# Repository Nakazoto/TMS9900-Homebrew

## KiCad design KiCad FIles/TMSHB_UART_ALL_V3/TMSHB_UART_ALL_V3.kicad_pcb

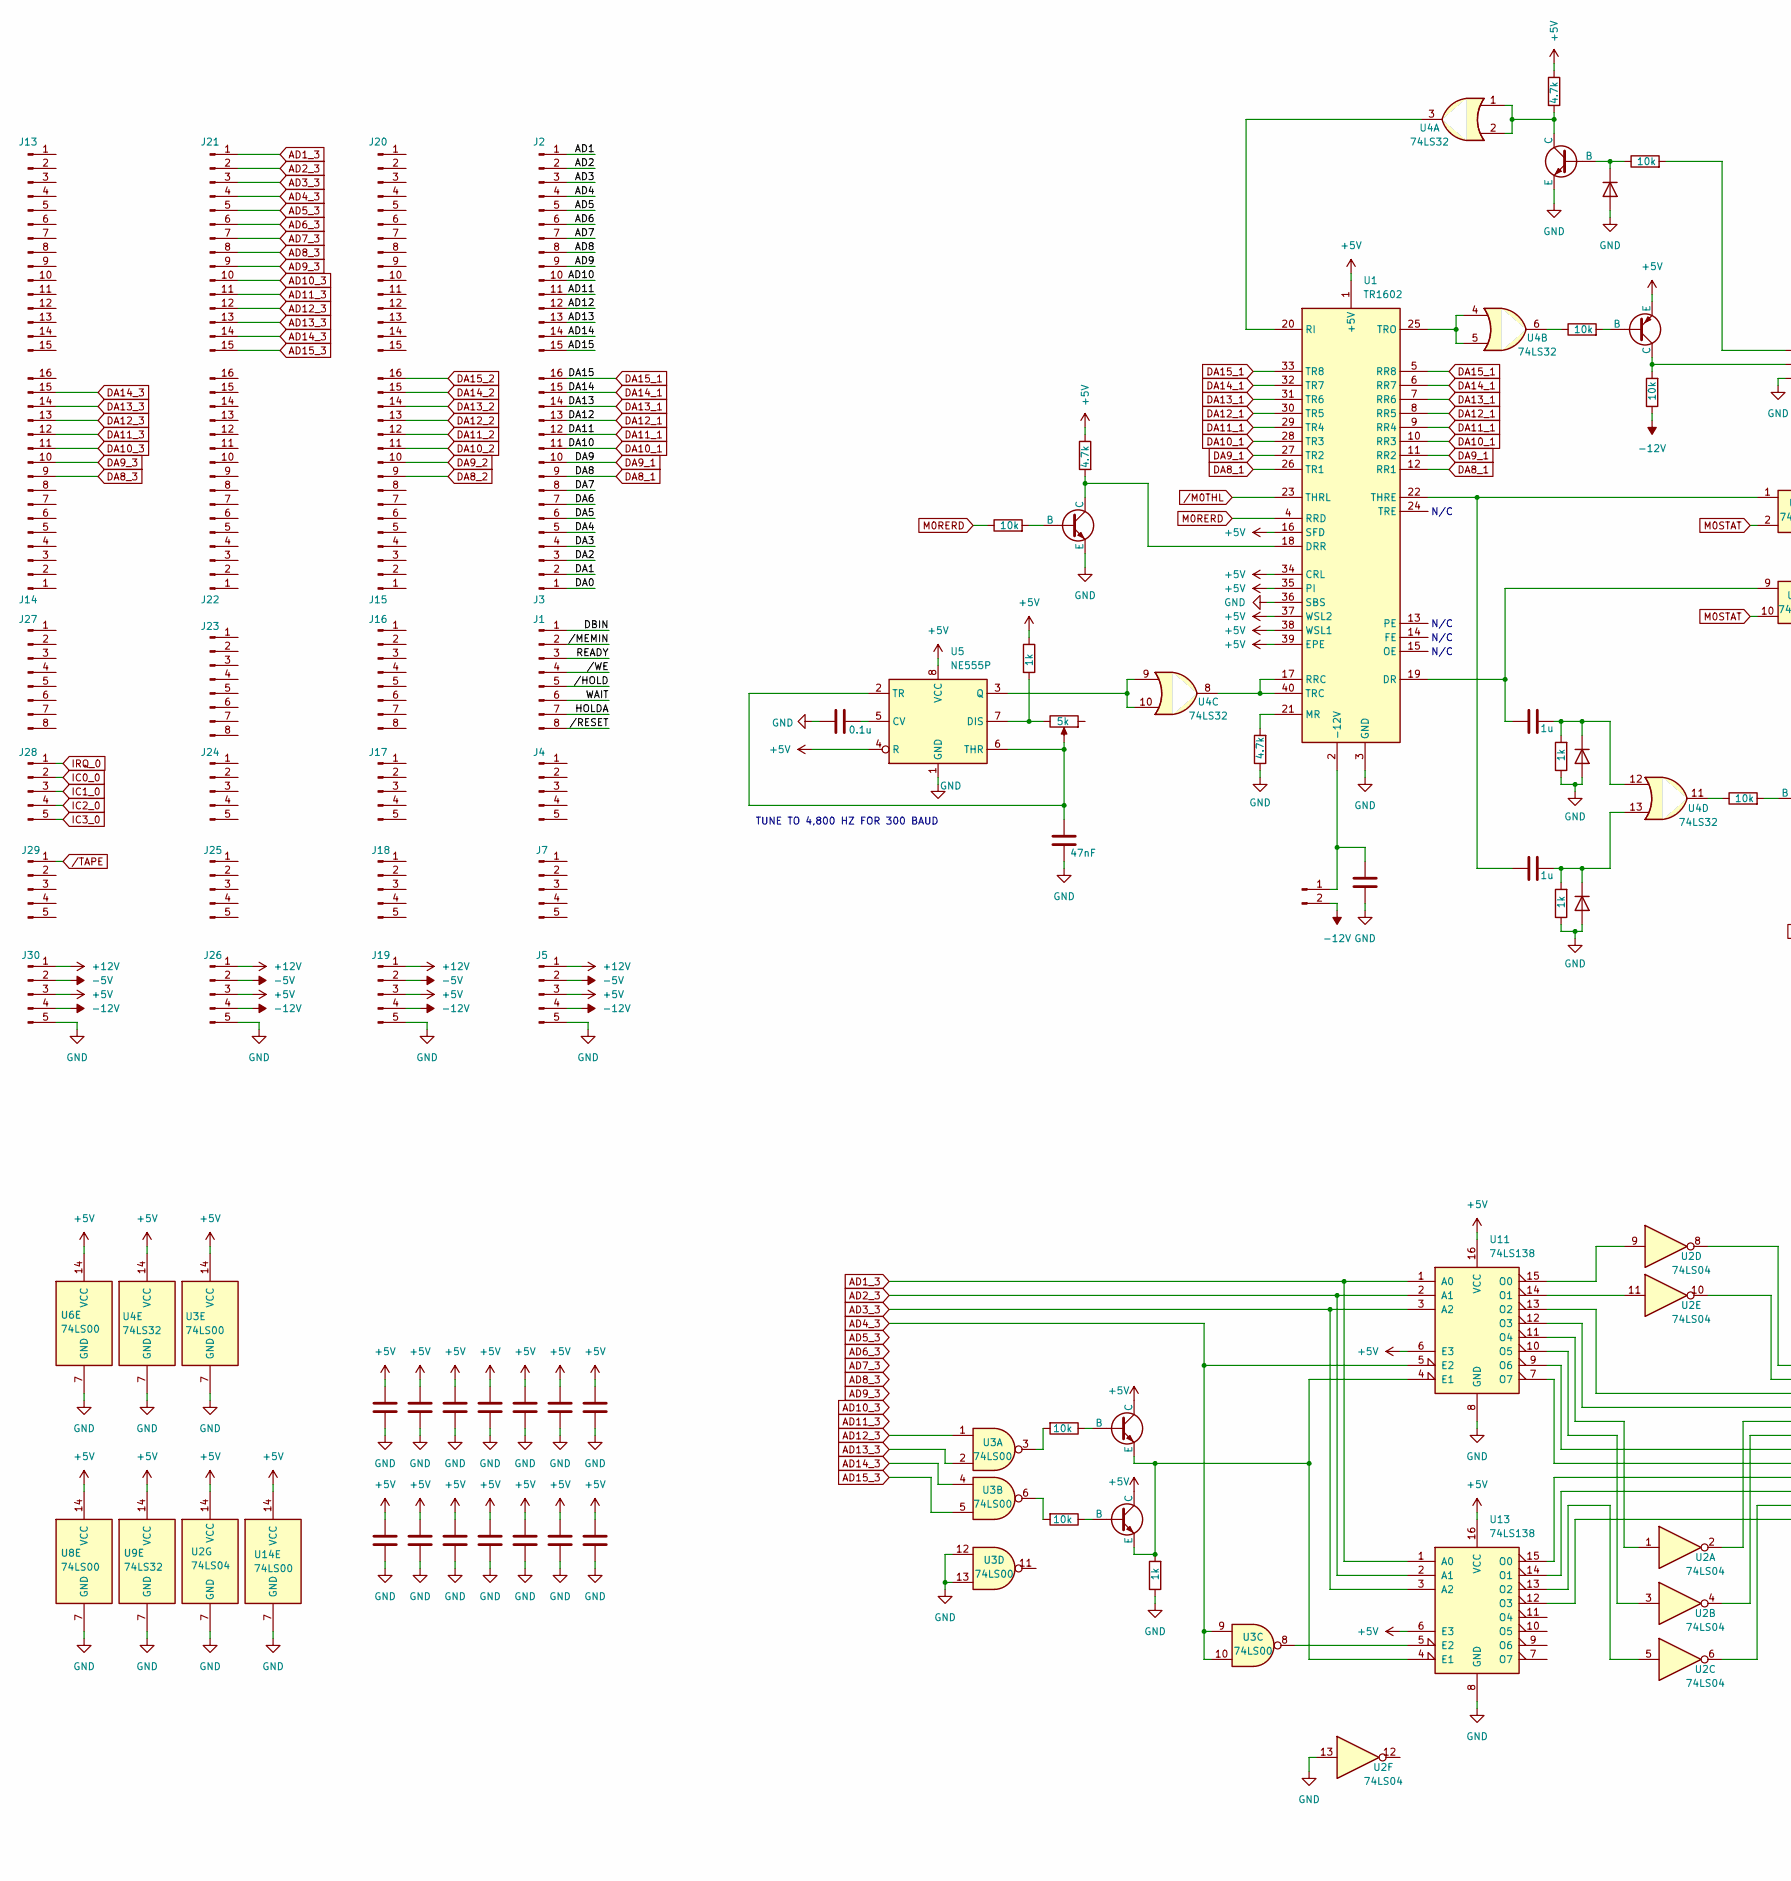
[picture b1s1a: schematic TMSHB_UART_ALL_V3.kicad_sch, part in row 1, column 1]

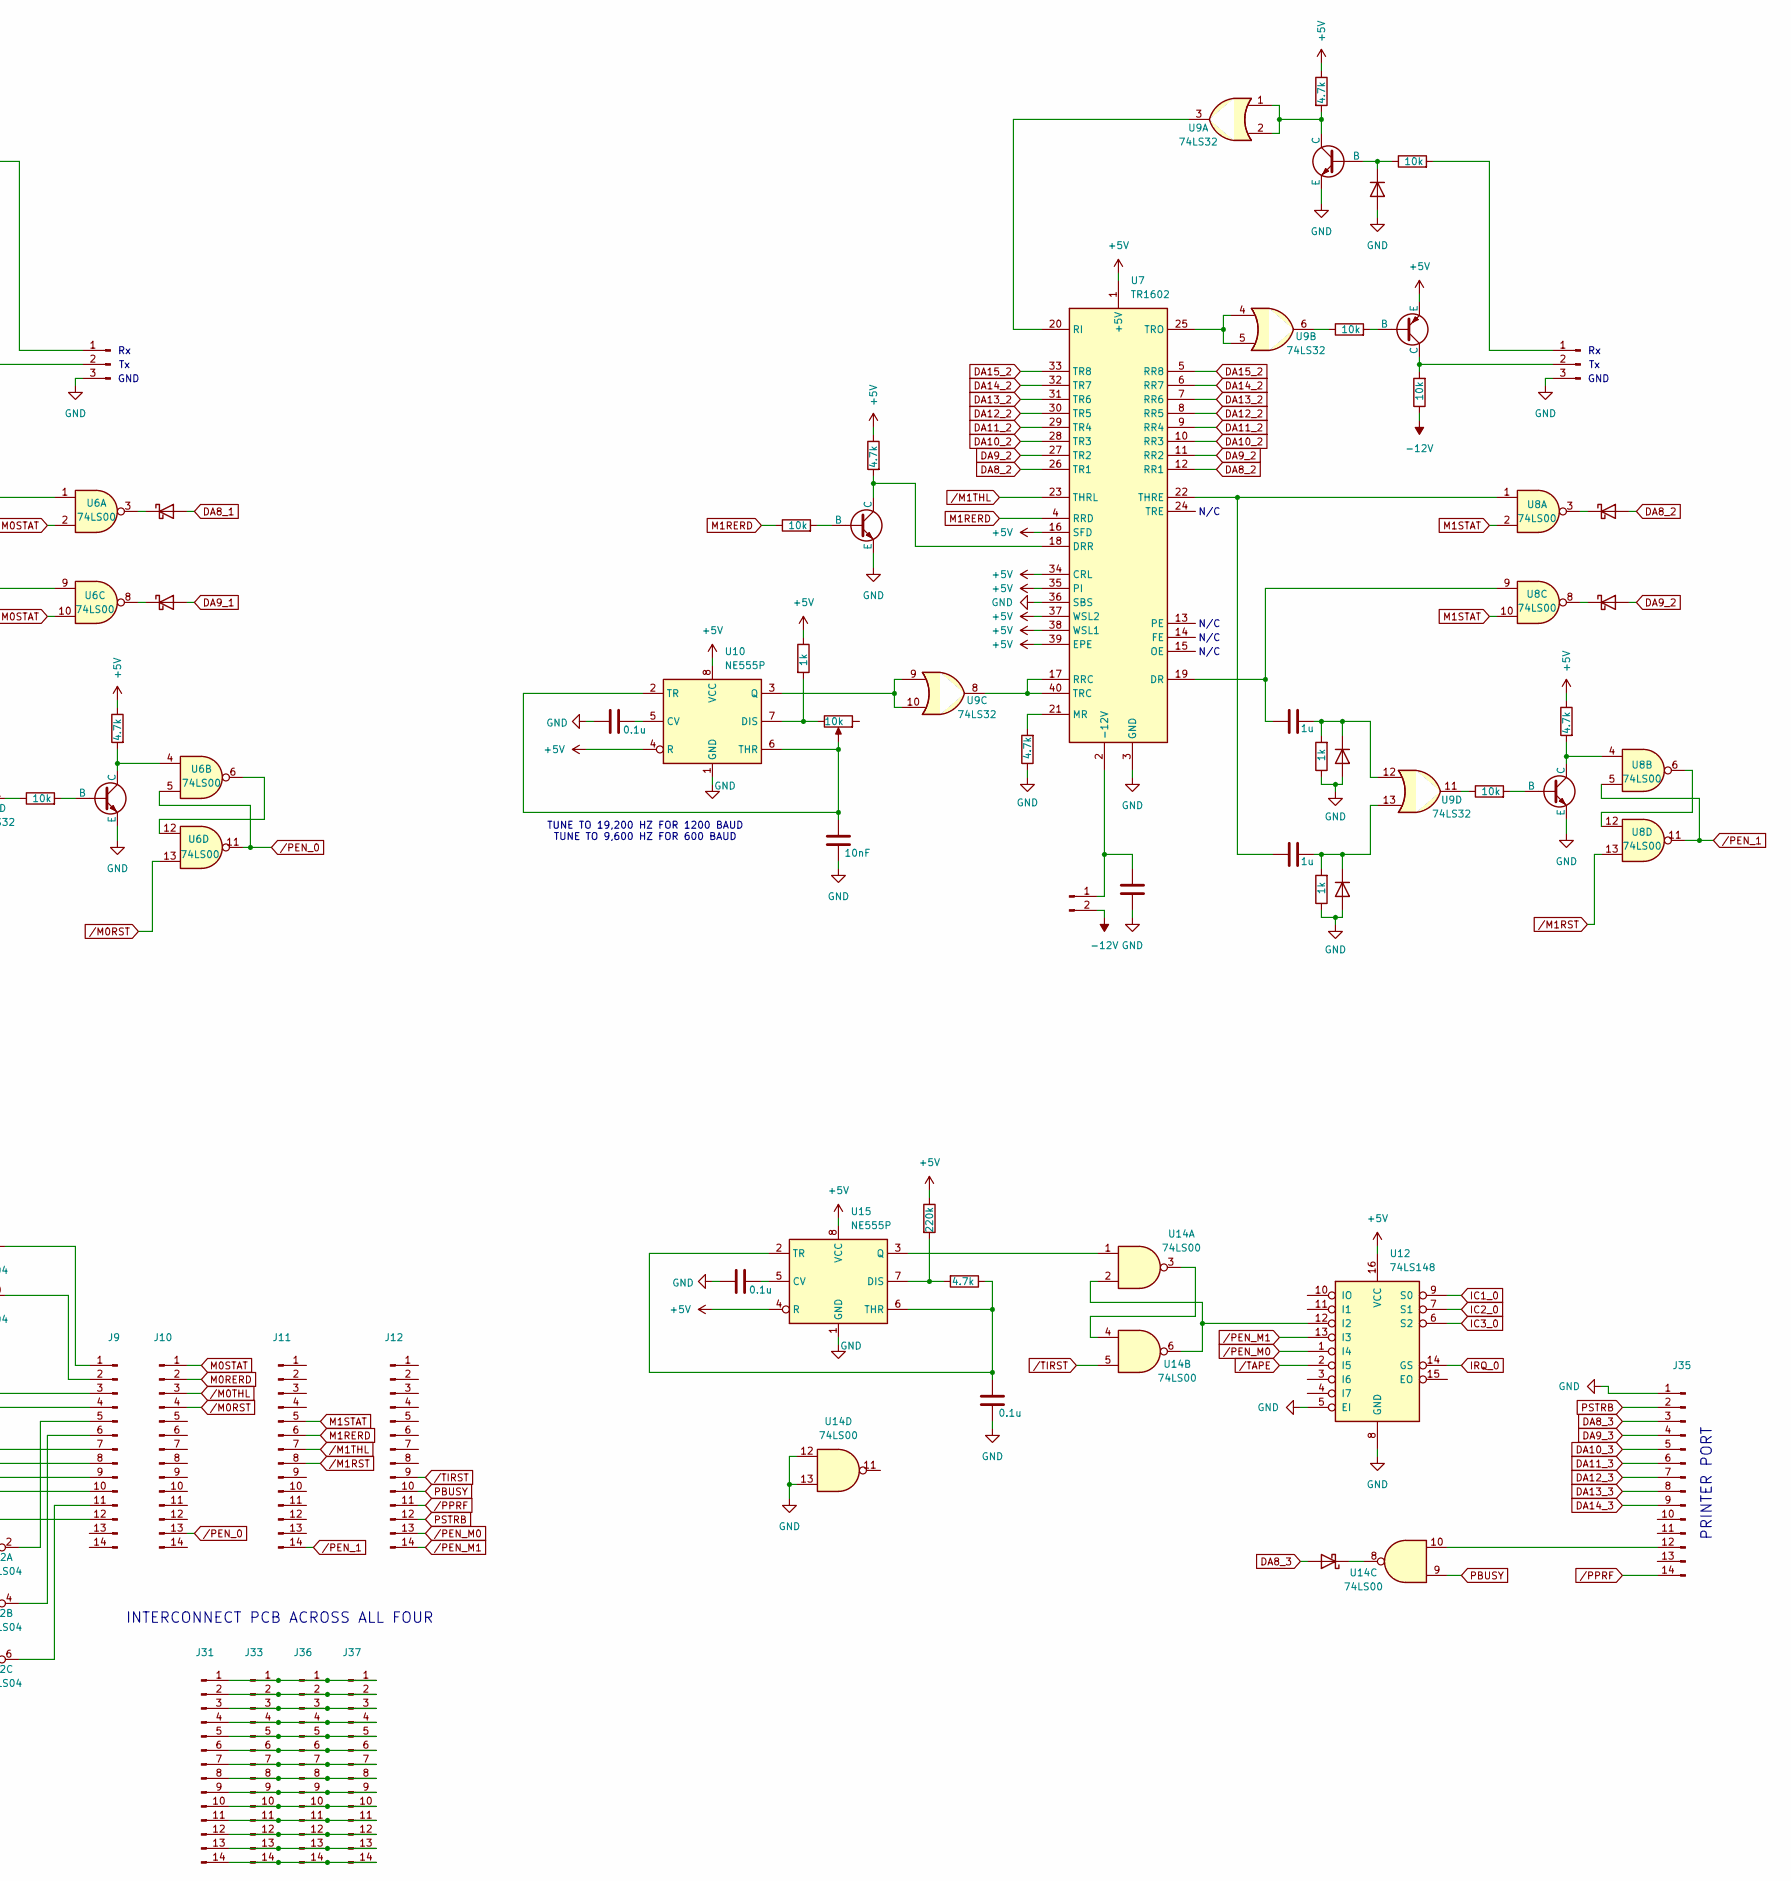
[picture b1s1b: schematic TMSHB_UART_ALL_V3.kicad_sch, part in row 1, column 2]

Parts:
C1, C2, C3, C6, C9, C10, C11, C12, C13, C14, C15, C16, C17, C18, C21, C22: C; C_Disc_D3.0mm_W1.6mm_P2.50mm
C4: 47nF; C_Disc_D3.0mm_W1.6mm_P2.50mm
C5, C7, C23, C24: 0.1u; C_Disc_D3.0mm_W1.6mm_P2.50mm
C8: 10nF; C_Disc_D3.0mm_W1.6mm_P2.50mm
C19, C20, C25, C26: 1u; C_Disc_D3.0mm_W1.6mm_P2.50mm
D1, D2, D3, D7, D8, D18: D; D_DO-34_SOD68_P7.62mm_Horizontal
D4, D5, D6, D19, D20: D_Schottky; D_DO-34_SOD68_P7.62mm_Horizontal
J1, J16, J23, J27: Conn_01x08_Pin; PinHeader_1x08_P2.54mm_Vertical
J2, J13, J20, J21: Conn_01x15_Pin; PinHeader_1x15_P2.54mm_Vertical
J3, J14, J15, J22: Conn_01x16_Pin; PinHeader_1x16_P2.54mm_Vertical
J4, J5, J7, J17, J18, J19, J24, J25, J26, J28, J29, J30: Conn_01x05_Pin; PinHeader_1x05_P2.54mm_Vertical
J6, J8: Conn_01x03_Pin; PinHeader_1x03_P2.54mm_Vertical
J9: Interconnect; PinHeader_1x14_P2.54mm_Vertical
J10, J11, J12, J31, J33, J35, J36, J37: Conn_01x14_Pin; PinHeader_1x14_P2.54mm_Vertical
J32, J34: Conn_01x02_Pin; PinHeader_1x02_P2.54mm_Vertical
Q1, Q3, Q4, Q5, Q6, Q7, Q8, Q13: NPN; TO-92_Inline_Wide
Q2, Q14: PNP; TO-92_Inline_Wide
R1, R3, R9, R11, R15, R16, R19, R22, R27: 4.7k; R_Axial_DIN0207_L6.3mm_D2.5mm_P10.16mm_Horizontal
R2, R4, R8, R13, R17, R20, R26: 1k; R_Axial_DIN0207_L6.3mm_D2.5mm_P10.16mm_Horizontal
R5, R6, R7, R10, R12, R18, R21, R23, R24, R25, R28, R29: 10k; R_Axial_DIN0207_L6.3mm_D2.5mm_P10.16mm_Horizontal
R14: 220k; R_Axial_DIN0207_L6.3mm_D2.5mm_P10.16mm_Horizontal
RV1: 5k; Potentiometer_Bourns_3296W_Vertical
RV2: 10k; Potentiometer_Bourns_3296W_Vertical
U1, U7: TR1602; DIP-40_W15.24mm
U2: 74LS04; DIP-14_W7.62mm
U3, U6, U8, U14: 74LS00; DIP-14_W7.62mm
U4, U9: 74LS32; DIP-14_W7.62mm
U5, U10, U15: NE555P; DIP-8_W7.62mm
U11, U13: 74LS138; DIP-16_W7.62mm
U12: 74LS148; DIP-16_W7.62mm

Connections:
+5V: C1.1, C2.1, C3.1, C6.1, C9.1, C10.1, C11.1, C12.1, C13.1, C14.1, C15.1, C16.1, C18.1, C22.1, J5.3, J19.3, J26.3, J30.3, Q2.3 (E), Q7.1 (C), Q8.1 (C), Q14.3 (E), R1.1, R4.1, R9.1, R11.1, R14.1, R19.1, R22.1, R26.1, R27.1, U1.1 (+5V), U1.16 (SFD), U1.34 (CRL), U1.35 (PI), U1.37 (WSL2), U1.38 (WSL1), U1.39 (EPE), U2.14 (VCC), U3.14 (VCC), U4.14 (VCC), U5.4 (R), U5.8 (VCC), U6.14 (VCC), U7.1 (+5V), U7.16 (SFD), U7.34 (CRL), U7.35 (PI), U7.37 (WSL2), U7.38 (WSL1), U7.39 (EPE), U8.14 (VCC), U9.14 (VCC), U10.4 (R), U10.8 (VCC), U11.6 (E3), U11.16 (VCC), U12.16 (VCC), U13.6 (E3), U13.16 (VCC), U14.14 (VCC), U15.4 (R), U15.8 (VCC)
+12V: J5.1, J19.1, J26.1, J30.1
-5V: J5.2, J19.2, J26.2, J30.2
-12V: J5.4, J19.4, J26.4, J30.4, J32.2, J34.2, R7.1, R25.1
/AD1: J2.1
/AD2: J2.2
/AD3: J2.3
/AD4: J2.4
/AD5: J2.5
/AD6: J2.6
/AD7: J2.7
/AD8: J2.8
/AD9: J2.9
/AD10: J2.10
/AD11: J2.11
/AD12: J2.12
/AD13: J2.13
/AD14: J2.14
/AD15: J2.15
/DA0: J3.1
/DA1: J3.2
/DA2: J3.3
/DA3: J3.4
/DA4: J3.5
/DA5: J3.6
/DA6: J3.7
/DA7: J3.8
/DBIN: J1.1
/HOLDA: J1.7
/READY: J1.3
/WAIT: J1.6
//HOLD: J1.5
//MEMIN: J1.2
//RESET: J1.8
//WE: J1.4
AD1_3: J21.1, U11.1 (A0), U13.1 (A0)
AD2_3: J21.2, U11.2 (A1), U13.2 (A1)
AD3_3: J21.3, U11.3 (A2), U13.3 (A2)
AD4_3: J21.4, U3.9, U3.10, U11.5 (E2)
AD5_3: J21.5
AD6_3: J21.6
AD7_3: J21.7
AD8_3: J21.8
AD9_3: J21.9
AD10_3: J21.10
AD11_3: J21.11
AD12_3: J21.12, U3.1
AD13_3: J21.13, U3.2
AD14_3: J21.14, U3.4
AD15_3: J21.15, U3.5
DA8_1: D4.2 (A), J3.9, U1.12 (RR1), U1.26 (TR1)
DA8_2: D19.2 (A), J15.9, U7.12 (RR1), U7.26 (TR1)
DA8_3: D6.2 (A), J14.9, J35.3
DA9_1: D5.2 (A), J3.10, U1.11 (RR2), U1.27 (TR2)
DA9_2: D20.2 (A), J15.10, U7.11 (RR2), U7.27 (TR2)
DA9_3: J14.10, J35.4
DA10_1: J3.11, U1.10 (RR3), U1.28 (TR3)
DA10_2: J15.11, U7.10 (RR3), U7.28 (TR3)
DA10_3: J14.11, J35.5
DA11_1: J3.12, U1.9 (RR4), U1.29 (TR4)
DA11_2: J15.12, U7.9 (RR4), U7.29 (TR4)
DA11_3: J14.12, J35.6
DA12_1: J3.13, U1.8 (RR5), U1.30 (TR5)
DA12_2: J15.13, U7.8 (RR5), U7.30 (TR5)
DA12_3: J14.13, J35.7
DA13_1: J3.14, U1.7 (RR6), U1.31 (TR6)
DA13_2: J15.14, U7.7 (RR6), U7.31 (TR6)
DA13_3: J14.14, J35.8
DA14_1: J3.15, U1.6 (RR7), U1.32 (TR7)
DA14_2: J15.15, U7.6 (RR7), U7.32 (TR7)
DA14_3: J14.15, J35.9
DA15_1: J3.16, U1.5 (RR8), U1.33 (TR8)
DA15_2: J15.16, U7.5 (RR8), U7.33 (TR8)
GND: C1.2, C2.2, C3.2, C4.2, C5.1, C6.2, C7.1, C8.2, C9.2, C10.2, C11.2, C12.2, C13.2, C14.2, C15.2, C16.2, C17.2, C18.2, C21.2, C22.2, C23.1, C24.2, D1.2 (A), D2.2 (A), D3.2 (A), D7.2 (A), D8.2 (A), D18.2 (A), J5.5, J6.3, J8.3, J19.5, J26.5, J30.5, J35.1, Q1.3 (E), Q3.3 (E), Q4.3 (E), Q5.3 (E), Q6.3 (E), Q13.3 (E), R2.1, R3.1, R8.1, R13.1, R16.1, R17.1, R20.1, U1.3 (GND), U1.36 (SBS), U2.7 (GND), U2.13, U3.7 (GND), U3.12, U3.13, U4.7 (GND), U5.1 (GND), U6.7 (GND), U7.3 (GND), U7.36 (SBS), U8.7 (GND), U9.7 (GND), U10.1 (GND), U11.8 (GND), U12.5 (EI), U12.8 (GND), U13.8 (GND), U14.7 (GND), U14.12, U14.13, U15.1 (GND)
IC0_0: J28.2
IC1_0: J28.3, U12.9 (S0)
IC2_0: J28.4, U12.7 (S1)
IC3_0: J28.5, U12.6 (S2)
IRQ_0: J28.1, U12.14 (GS)
M0RERD: J10.2, R18.1, U1.4 (RRD)
M0STAT: J10.1, U6.2, U6.10
M1RERD: J11.6, R21.1, U7.4 (RRD)
M1STAT: J11.5, U8.2, U8.10
unnamed: D1.1 (K), Q3.2 (B), R10.1
unnamed: D2.1 (K), Q13.2 (B), R24.1
unnamed: C19.2, D3.1 (K), R2.2, U4.13
unnamed: D4.1 (K), U6.3
unnamed: D5.1 (K), U6.8
unnamed: D6.1 (K), U14.8
unnamed: C25.2, D7.1 (K), R17.2, U4.12
unnamed: C26.2, D8.1 (K), R20.2, U9.12
unnamed: C20.2, D18.1 (K), R13.2, U9.13
unnamed: D19.1 (K), U8.3
unnamed: D20.1 (K), U8.8
unnamed: J6.1, R10.2
unnamed: J6.2, Q2.1 (C), R7.2
unnamed: J8.1, R24.2
unnamed: J8.2, Q14.1 (C), R25.2
unnamed: J9.1, U2.8
unnamed: J9.2, U2.10
unnamed: J9.3, U11.13 (O2)
unnamed: J9.4, U11.12 (O3)
unnamed: J9.5, U2.2
unnamed: J9.6, U2.4
unnamed: J9.7, U11.9 (O6)
unnamed: J9.8, U11.7 (O7)
unnamed: J9.9, U13.15 (O0)
unnamed: J9.10, U13.14 (O1)
unnamed: J9.11, U2.6
unnamed: J9.12, U13.12 (O3)
unnamed: J31.1, J33.1, J36.1, J37.1
unnamed: J31.2, J33.2, J36.2, J37.2
unnamed: J31.3, J33.3, J36.3, J37.3
unnamed: J31.4, J33.4, J36.4, J37.4
unnamed: J31.5, J33.5, J36.5, J37.5
unnamed: J31.6, J33.6, J36.6, J37.6
unnamed: J31.7, J33.7, J36.7, J37.7
unnamed: J31.8, J33.8, J36.8, J37.8
unnamed: J31.9, J33.9, J36.9, J37.9
unnamed: J31.10, J33.10, J36.10, J37.10
unnamed: J31.11, J33.11, J36.11, J37.11
unnamed: J31.12, J33.12, J36.12, J37.12
unnamed: J31.13, J33.13, J36.13, J37.13
unnamed: J31.14, J33.14, J36.14, J37.14
unnamed: C17.1, J32.1, U1.2 (-12V)
unnamed: C21.1, J34.1, U7.2 (-12V)
unnamed: J35.12, U14.10
unnamed: Q1.2 (B), R5.2
unnamed: Q1.1 (C), R1.2, U6.4
unnamed: Q2.2 (B), R6.2
unnamed: Q3.1 (C), R11.2, U4.1, U4.2
unnamed: Q4.2 (B), R12.2
unnamed: Q4.1 (C), R9.2, U8.4
unnamed: Q5.2 (B), R18.2
unnamed: Q5.1 (C), R19.2, U1.18 (DRR)
unnamed: Q6.2 (B), R21.2
unnamed: Q6.1 (C), R27.2, U7.18 (DRR)
unnamed: Q7.2 (B), R28.1
unnamed: Q7.3 (E), Q8.3 (E), R8.2, U11.4 (E1), U13.4 (E1)
unnamed: Q8.2 (B), R29.1
unnamed: Q13.1 (C), R22.2, U9.1, U9.2
unnamed: Q14.2 (B), R23.2
unnamed: R5.1, U4.11
unnamed: R6.1, U4.6
unnamed: R12.1, U9.11
unnamed: R23.1, U9.6
unnamed: R28.2, U3.6
unnamed: R29.2, U3.3
unnamed: C25.1, U1.19 (DR), U6.9
unnamed: R3.2, U1.21 (MR)
unnamed: U1.20 (RI), U4.3
unnamed: U1.17 (RRC), U1.40 (TRC), U4.8
unnamed: C19.1, U1.22 (THRE), U6.1
unnamed: U1.25 (TRO), U4.4, U4.5
unnamed: C5.2, U5.5 (CV)
unnamed: R4.2, RV1.3, U5.7 (DIS)
unnamed: U4.9, U4.10, U5.3 (Q)
unnamed: C4.1, RV1.2, U5.2 (TR), U5.6 (THR)
unnamed: U6.6, U6.12
unnamed: C26.1, U7.19 (DR), U8.9
unnamed: R16.2, U7.21 (MR)
unnamed: U7.20 (RI), U9.3
unnamed: U7.17 (RRC), U7.40 (TRC), U9.8
unnamed: C20.1, U7.22 (THRE), U8.1
unnamed: U7.25 (TRO), U9.4, U9.5
unnamed: U8.6, U8.12
unnamed: C7.2, U10.5 (CV)
unnamed: R26.2, RV2.3, U10.7 (DIS)
unnamed: U9.9, U9.10, U10.3 (Q)
unnamed: C8.1, RV2.2, U10.2 (TR), U10.6 (THR)
unnamed: U2.9, U11.15 (O0)
unnamed: U2.11, U11.14 (O1)
unnamed: U2.1, U11.11 (O4)
unnamed: U2.3, U11.10 (O5)
unnamed: U12.12 (I2), U14.2, U14.6
unnamed: U3.8, U13.5 (E2)
unnamed: U2.5, U13.13 (O2)
unnamed: U14.3, U14.4
unnamed: C23.2, U15.5 (CV)
unnamed: R14.2, R15.2, U15.7 (DIS)
unnamed: U14.1, U15.3 (Q)
unnamed: C24.1, R15.1, U15.2 (TR), U15.6 (THR)
PBUSY: J12.10, U14.9
PSTRB: J12.12, J35.2
/M0RST: J10.4, U6.13
/M0THL: J10.3, U1.23 (THRL)
/M1RST: J11.8, U8.13
/M1THL: J11.7, U7.23 (THRL)
/PEN_0: J10.13, U6.5, U6.11
/PEN_1: J11.14, U8.5, U8.11
/PEN_M0: J12.13, U12.1 (I4)
/PEN_M1: J12.14, U12.13 (I3)
/PPRF: J12.11, J35.14
/TAPE: J29.1, U12.2 (I5)
/TIRST: J12.9, U14.5

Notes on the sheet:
GND
TUNE TO 19,200 HZ FOR 1200 BAUD TUNE TO 9,600 HZ FOR 600 BAUD
N/C
TUNE TO 4,800 HZ FOR 300 BAUD
INTERCONNECT PCB ACROSS ALL FOUR
PRINTER PORT

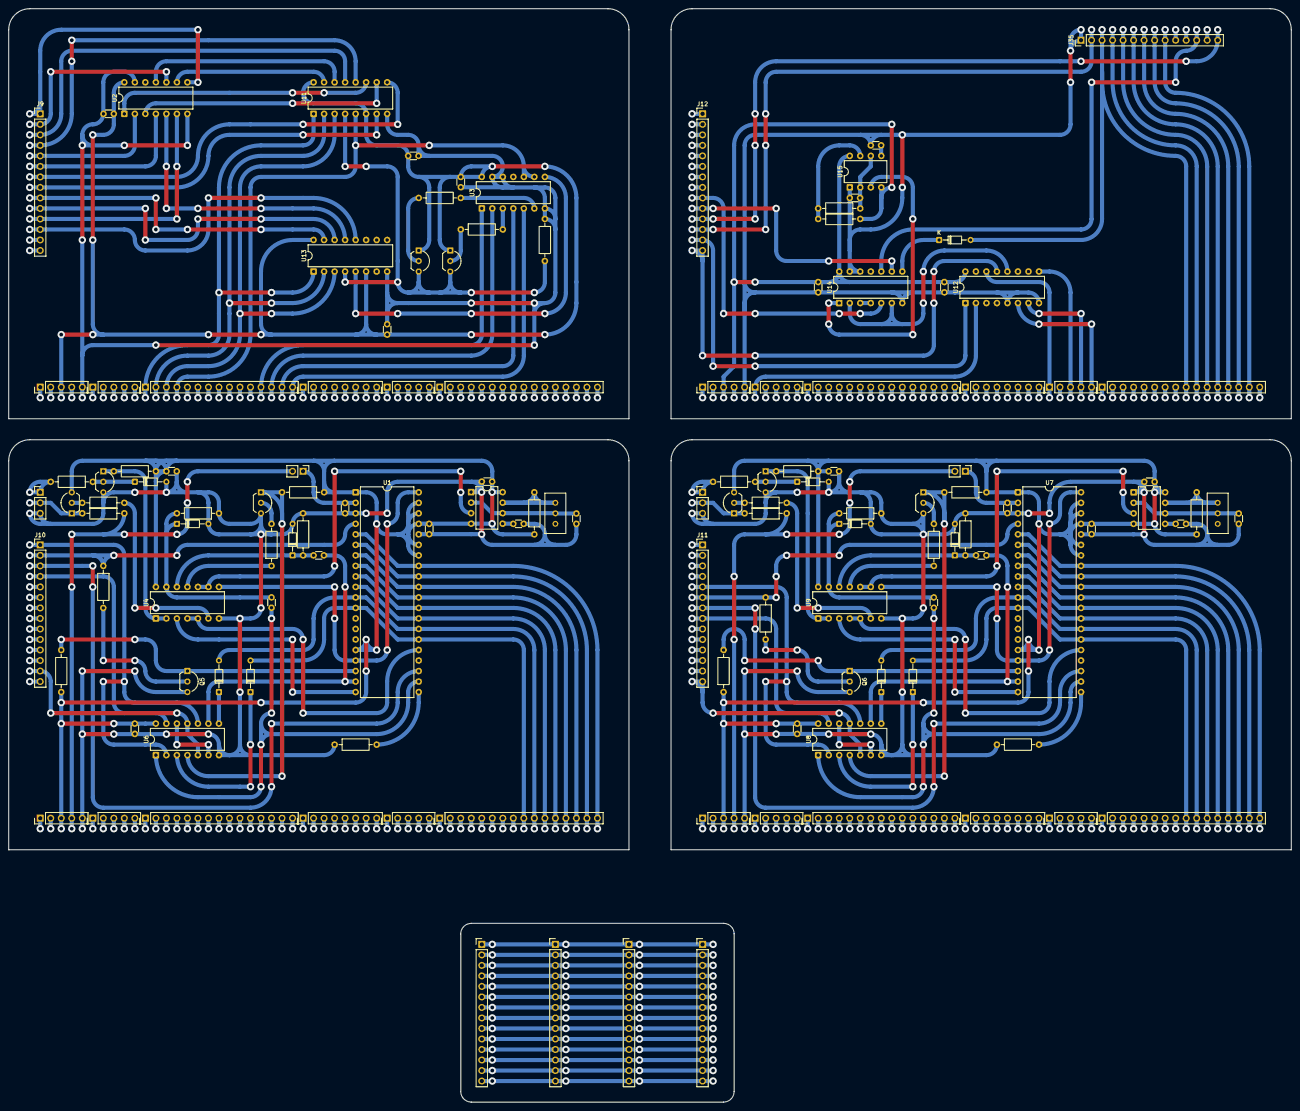
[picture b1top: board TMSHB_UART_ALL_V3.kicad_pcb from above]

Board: 2 copper layers, 309.9 x 264.2 mm, 130 parts (0 on the bottom side), 156 nets.

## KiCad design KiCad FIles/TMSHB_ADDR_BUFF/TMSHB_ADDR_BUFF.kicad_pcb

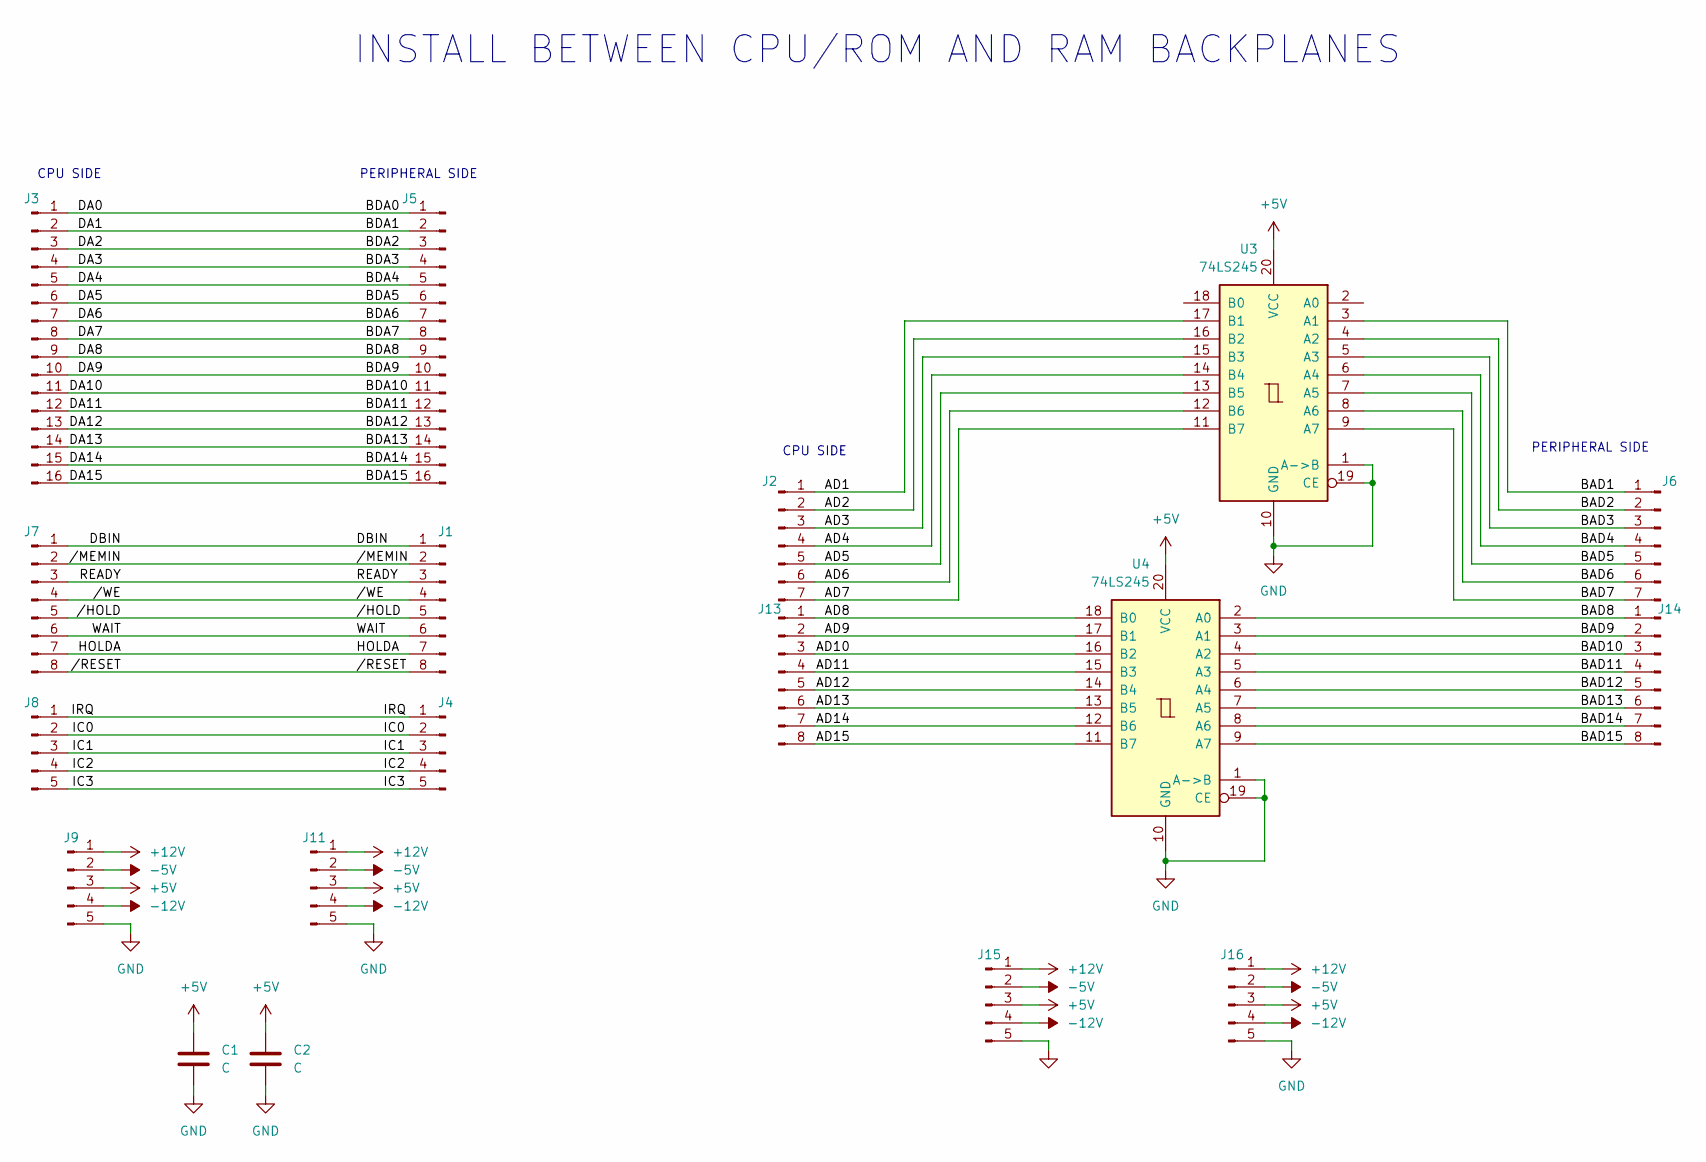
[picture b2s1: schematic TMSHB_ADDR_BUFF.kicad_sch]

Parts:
C1, C2: C; C_Disc_D3.0mm_W1.6mm_P2.50mm
J1, J7, J13, J14: Conn_01x08_Pin; PinHeader_1x08_P2.54mm_Vertical
J2, J6: Conn_01x07_Pin; PinHeader_1x07_P2.54mm_Vertical
J3, J5: Conn_01x16_Pin; PinHeader_1x16_P2.54mm_Vertical
J4, J8, J9, J11, J15, J16: Conn_01x05_Pin; PinHeader_1x05_P2.54mm_Vertical
U3, U4: 74LS245; DIP-20_W7.62mm

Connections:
+5V: C1.1, C2.1, J9.3, J11.3, J15.3, J16.3, U3.20 (VCC), U4.20 (VCC)
+12V: J9.1, J11.1, J15.1, J16.1
-5V: J9.2, J11.2, J15.2, J16.2
-12V: J9.4, J11.4, J15.4, J16.4
/AD1: J2.1, U3.17 (B1)
/AD2: J2.2, U3.16 (B2)
/AD3: J2.3, U3.15 (B3)
/AD4: J2.4, U3.14 (B4)
/AD5: J2.5, U3.13 (B5)
/AD6: J2.6, U3.12 (B6)
/AD7: J2.7, U3.11 (B7)
/AD8: J13.1, U4.18 (B0)
/AD9: J13.2, U4.17 (B1)
/AD10: J13.3, U4.16 (B2)
/AD11: J13.4, U4.15 (B3)
/AD12: J13.5, U4.14 (B4)
/AD13: J13.6, U4.13 (B5)
/AD14: J13.7, U4.12 (B6)
/AD15: J13.8, U4.11 (B7)
/BAD1: J6.1, U3.3 (A1)
/BAD2: J6.2, U3.4 (A2)
/BAD3: J6.3, U3.5 (A3)
/BAD4: J6.4, U3.6 (A4)
/BAD5: J6.5, U3.7 (A5)
/BAD6: J6.6, U3.8 (A6)
/BAD7: J6.7, U3.9 (A7)
/BAD8: J14.1, U4.2 (A0)
/BAD9: J14.2, U4.3 (A1)
/BAD10: J14.3, U4.4 (A2)
/BAD11: J14.4, U4.5 (A3)
/BAD12: J14.5, U4.6 (A4)
/BAD13: J14.6, U4.7 (A5)
/BAD14: J14.7, U4.8 (A6)
/BAD15: J14.8, U4.9 (A7)
/BDA0: J3.1, J5.1
/BDA1: J3.2, J5.2
/BDA2: J3.3, J5.3
/BDA3: J3.4, J5.4
/BDA4: J3.5, J5.5
/BDA5: J3.6, J5.6
/BDA6: J3.7, J5.7
/BDA7: J3.8, J5.8
/BDA8: J3.9, J5.9
/BDA9: J3.10, J5.10
/BDA10: J3.11, J5.11
/BDA11: J3.12, J5.12
/BDA12: J3.13, J5.13
/BDA13: J3.14, J5.14
/BDA14: J3.15, J5.15
/BDA15: J3.16, J5.16
/DBIN: J1.1, J7.1
/HOLDA: J1.7, J7.7
/IC0: J4.2, J8.2
/IC1: J4.3, J8.3
/IC2: J4.4, J8.4
/IC3: J4.5, J8.5
/IRQ: J4.1, J8.1
/READY: J1.3, J7.3
/WAIT: J1.6, J7.6
//HOLD: J1.5, J7.5
//MEMIN: J1.2, J7.2
//RESET: J1.8, J7.8
//WE: J1.4, J7.4
GND: C1.2, C2.2, J9.5, J11.5, J15.5, J16.5, U3.1 (A->B), U3.10 (GND), U3.19 (CE), U4.1 (A->B), U4.10 (GND), U4.19 (CE)

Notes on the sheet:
PERIPHERAL SIDE
INSTALL BETWEEN CPU/ROM AND RAM BACKPLANES
CPU SIDE

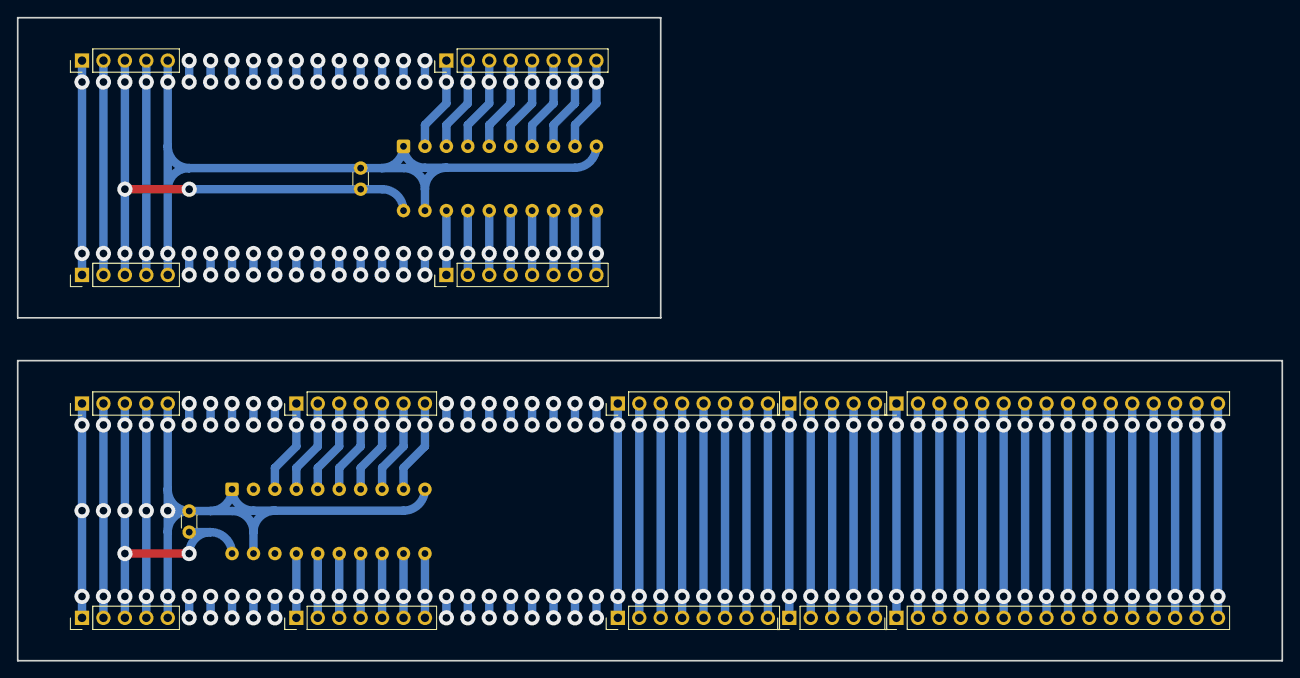
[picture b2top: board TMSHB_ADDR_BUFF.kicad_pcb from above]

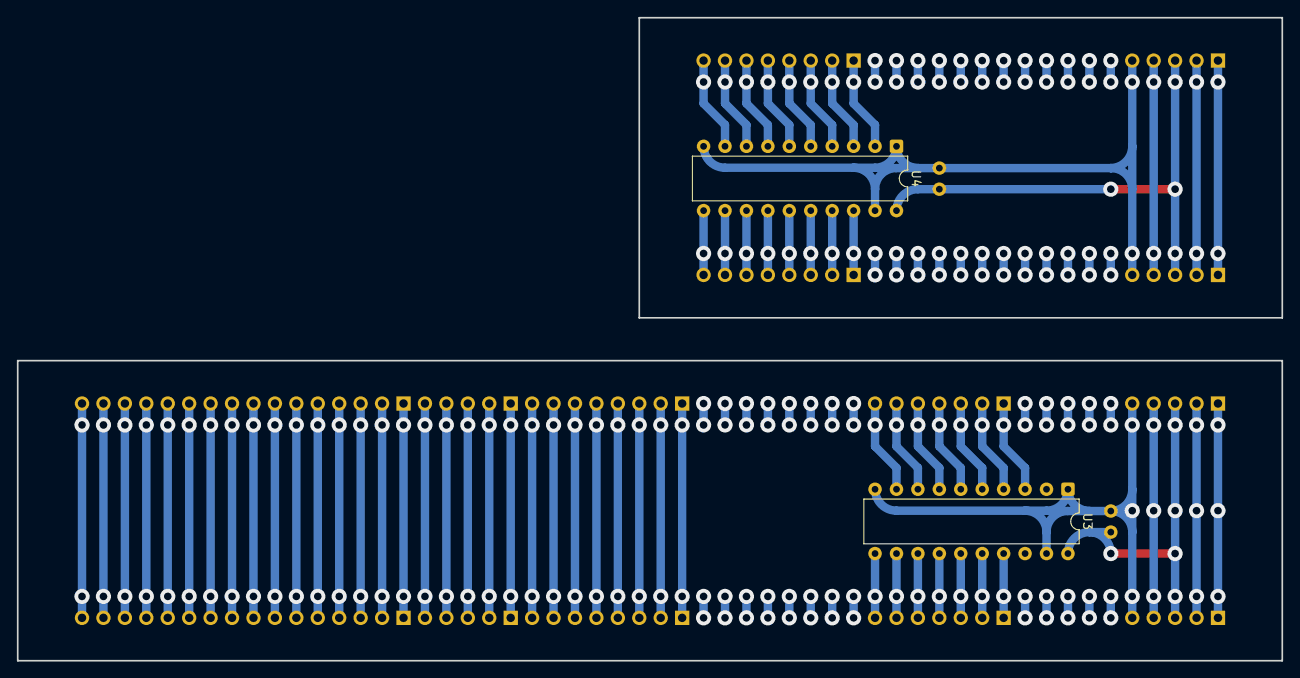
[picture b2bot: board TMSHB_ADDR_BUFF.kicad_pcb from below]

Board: 2 copper layers, 149.9 x 76.2 mm, 18 parts (2 on the bottom side), 64 nets.

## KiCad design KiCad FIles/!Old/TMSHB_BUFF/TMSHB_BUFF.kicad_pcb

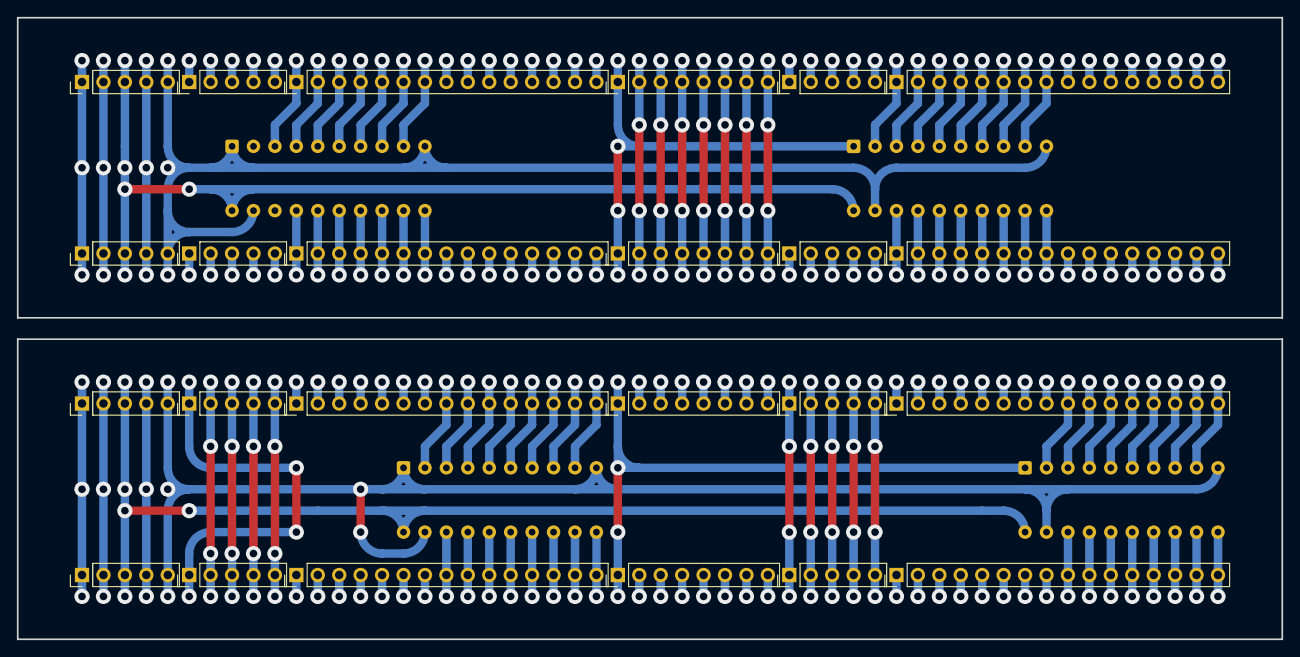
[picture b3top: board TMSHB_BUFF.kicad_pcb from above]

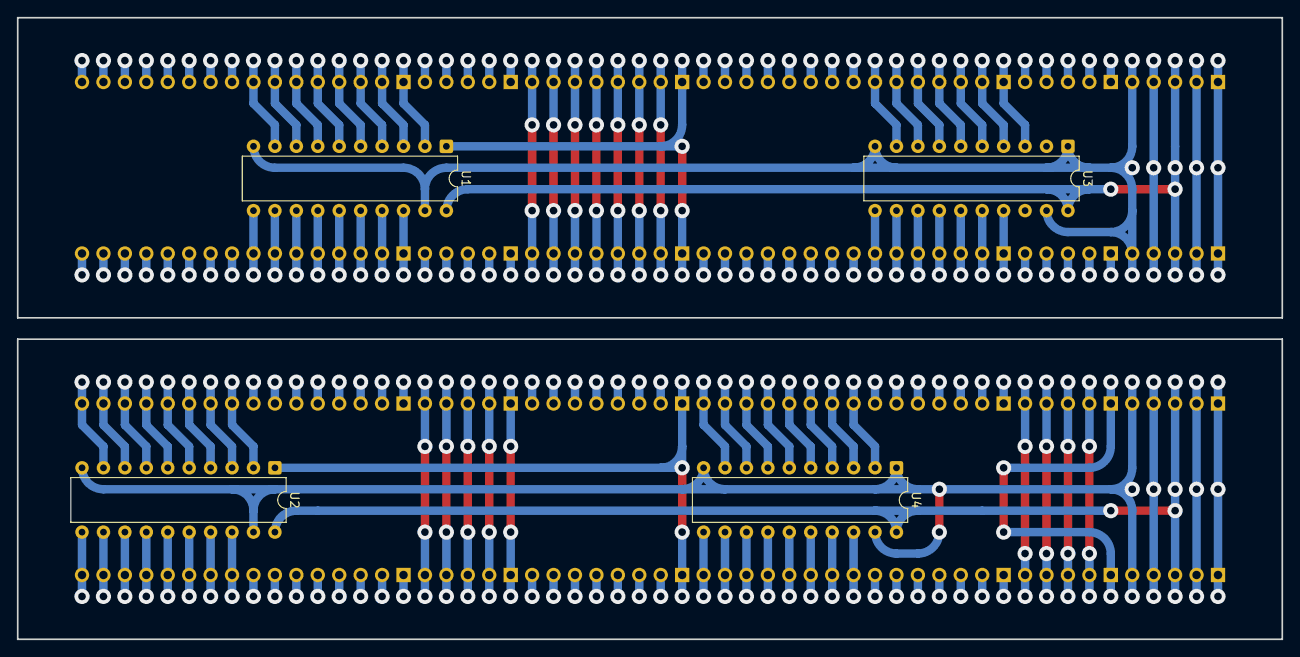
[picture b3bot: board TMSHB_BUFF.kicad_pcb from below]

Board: 2 copper layers, 149.9 x 73.7 mm, 28 parts (4 on the bottom side), 85 nets.

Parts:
J1, J7, J15, J16: Conn_01x08_Pin; PinHeader_1x08_P2.54mm_Vertical
J2, J6, J6#2, J6#3: Conn_01x15_Pin; PinHeader_1x15_P2.54mm_Vertical
J3, J3#2, J5, J5#2: Conn_01x16_Pin; PinHeader_1x16_P2.54mm_Vertical
J4, J4#2, J8, J8#2, J9, J10, J10#2, J11, J12, J12#2, J13, J14: Conn_01x05_Pin; PinHeader_1x05_P2.54mm_Vertical
U1, U2, U3, U4: 74LS245; DIP-20_W7.62mm

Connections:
+5V: J9.3, J11.3, J13.3, J14.3, U1.20 (VCC), U2.20 (VCC), U3.20 (VCC), U4.20 (VCC)
+12V: J9.1, J11.1, J13.1, J14.1
-5V: J9.2, J11.2, J13.2, J14.2
-12V: J9.4, J11.4, J13.4, J14.4
/AD1: J2.1, U3.17 (B1)
/AD2: J2.2, U3.16 (B2)
/AD3: J2.3, U3.15 (B3)
/AD4: J2.4, U3.14 (B4)
/AD5: J2.5, U3.13 (B5)
/AD6: J2.6, U3.12 (B6)
/AD7: J2.7, U3.11 (B7)
/AD8: J2.8, U4.18 (B0)
/AD9: J2.9, U4.17 (B1)
/AD10: J2.10, U4.16 (B2)
/AD11: J2.11, U4.15 (B3)
/AD12: J2.12, U4.14 (B4)
/AD13: J2.13, U4.13 (B5)
/AD14: J2.14, U4.12 (B6)
/AD15: J2.15, U4.11 (B7)
/BAD1: J6#3.1, U3.3 (A1)
/BAD2: J6#3.2, U3.4 (A2)
/BAD3: J6#3.3, U3.5 (A3)
/BAD4: J6#3.4, U3.6 (A4)
/BAD5: J6#3.5, U3.7 (A5)
/BAD6: J6#3.6, U3.8 (A6)
/BAD7: J6#3.7, U3.9 (A7)
/BAD8: J6#3.8, U4.2 (A0)
/BAD9: J6#3.9, U4.3 (A1)
/BAD10: J6#3.10, U4.4 (A2)
/BAD11: J6#3.11, U4.5 (A3)
/BAD12: J6#3.12, U4.6 (A4)
/BAD13: J6#3.13, U4.7 (A5)
/BAD14: J6#3.14, U4.8 (A6)
/BAD15: J6#3.15, U4.9 (A7)
/BDA0: J5.1, J5#2.1, U1.2 (A0)
/BDA1: J5.2, J5#2.2, U1.3 (A1)
/BDA2: J5.3, J5#2.3, U1.4 (A2)
/BDA3: J5.4, J5#2.4, U1.5 (A3)
/BDA4: J5.5, J5#2.5, U1.6 (A4)
/BDA5: J5.6, J5#2.6, U1.7 (A5)
/BDA6: J5.7, J5#2.7, U1.8 (A6)
/BDA7: J5.8, J5#2.8, U1.9 (A7)
/BDA8: J5.9, J5#2.9, U2.2 (A0)
/BDA9: J5.10, J5#2.10, U2.3 (A1)
/BDA10: J5.11, J5#2.11, U2.4 (A2)
/BDA11: J5.12, J5#2.12, U2.5 (A3)
/BDA12: J5.13, J5#2.13, U2.6 (A4)
/BDA13: J5.14, J5#2.14, U2.7 (A5)
/BDA14: J5.15, J5#2.15, U2.8 (A6)
/BDA15: J5.16, J5#2.16, U2.9 (A7)
/DA0: J3.1, J3#2.1, U1.18 (B0)
/DA1: J3.2, J3#2.2, U1.17 (B1)
/DA2: J3.3, J3#2.3, U1.16 (B2)
/DA3: J3.4, J3#2.4, U1.15 (B3)
/DA4: J3.5, J3#2.5, U1.14 (B4)
/DA5: J3.6, J3#2.6, U1.13 (B5)
/DA6: J3.7, J3#2.7, U1.12 (B6)
/DA7: J3.8, J3#2.8, U1.11 (B7)
/DA8: J3.9, J3#2.9, U2.18 (B0)
/DA9: J3.10, J3#2.10, U2.17 (B1)
/DA10: J3.11, J3#2.11, U2.16 (B2)
/DA11: J3.12, J3#2.12, U2.15 (B3)
/DA12: J3.13, J3#2.13, U2.14 (B4)
/DA13: J3.14, J3#2.14, U2.13 (B5)
/DA14: J3.15, J3#2.15, U2.12 (B6)
/DA15: J3.16, J3#2.16, U2.11 (B7)
/DBIN: J1.1, J7.1, J15.1, J16.1, U1.1 (A->B), U2.1 (A->B)
/HOLDA: J1.7, J7.7, J15.7, J16.7
/IC0: J4.2, J4#2.2, J8.2, J8#2.2
/IC1: J4.3, J4#2.3, J8.3, J8#2.3
/IC2: J4.4, J4#2.4, J8.4, J8#2.4
/IC3: J4.5, J4#2.5, J8.5, J8#2.5
/IRQ: J4.1, J4#2.1, J8.1, J8#2.1
/READY: J1.3, J7.3, J15.3, J16.3
/WAIT: J1.6, J7.6, J15.6, J16.6
//HOLD: J1.5, J7.5, J15.5, J16.5
//MEMIN: J1.2, J7.2, J15.2, J16.2
//RESET: J1.8, J7.8, J15.8, J16.8
//WE: J1.4, J7.4, J15.4, J16.4
GND: J9.5, J11.5, J13.5, J14.5, U1.10 (GND), U1.19 (CE), U2.10 (GND), U2.19 (CE), U3.1 (A->B), U3.10 (GND), U3.19 (CE), U4.1 (A->B), U4.10 (GND), U4.19 (CE)
unnamed: J10.1, J10#2.1, J12.1, J12#2.1
unnamed: J10.2, J10#2.2, J12.2, J12#2.2
unnamed: J10.3, J10#2.3, J12.3, J12#2.3
unnamed: J10.4, J10#2.4, J12.4, J12#2.4
unnamed: J10.5, J10#2.5, J12.5, J12#2.5
